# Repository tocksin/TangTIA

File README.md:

# TangTIA
Atari TIA monitor with Tang Nano for HDMI output

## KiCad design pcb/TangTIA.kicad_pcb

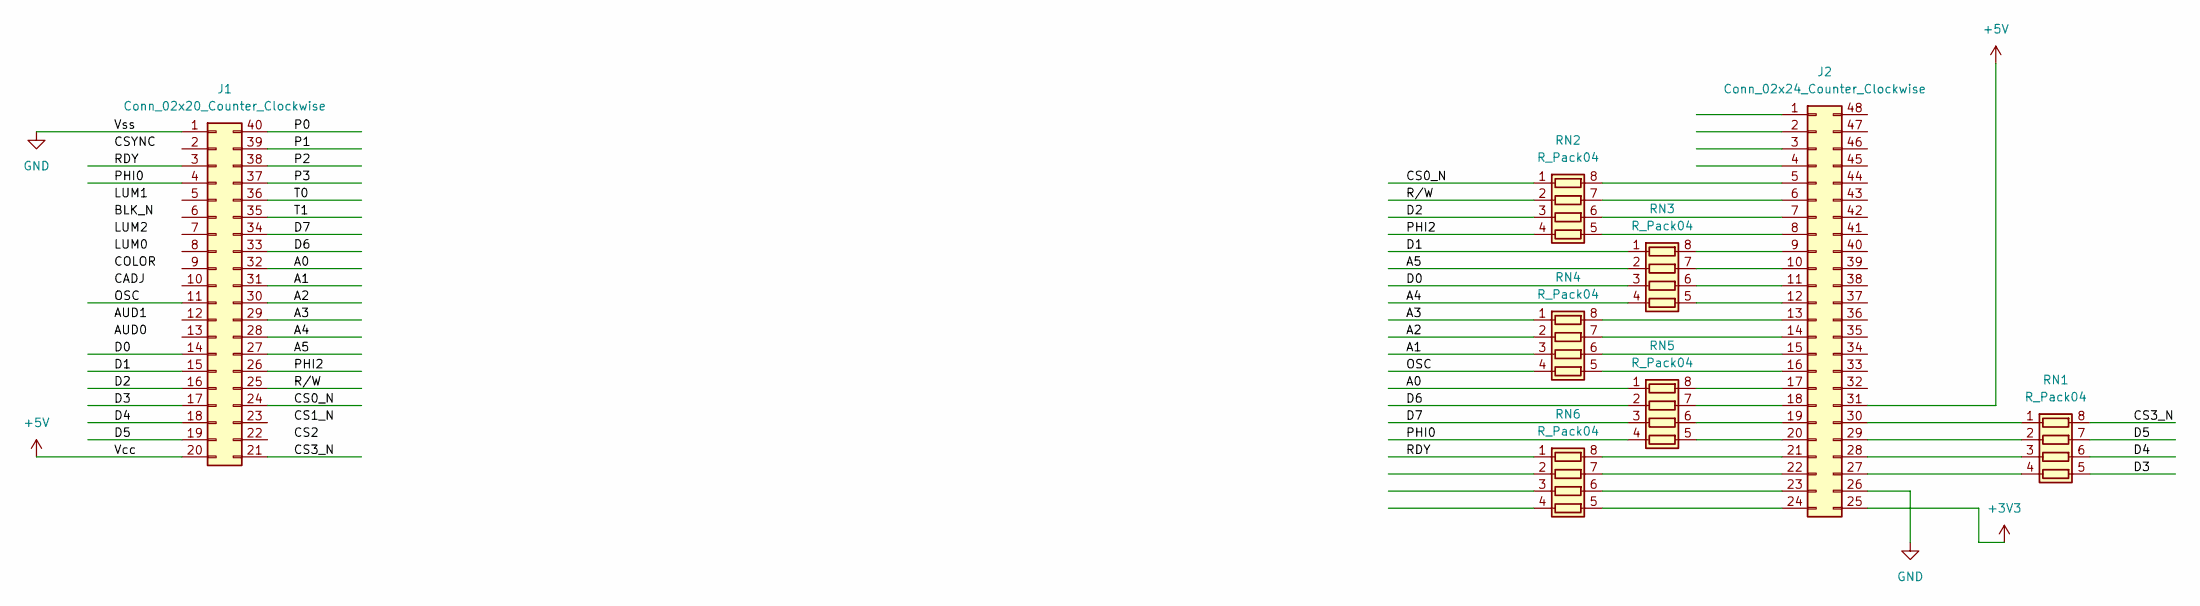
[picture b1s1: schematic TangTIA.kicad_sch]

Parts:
J1: Conn_02x20_Counter_Clockwise; DIP-40_W15.24mm_Socket_LongPads
J2: Conn_02x24_Counter_Clockwise; DIP-48_W15.24mm_Socket_LongPads
RN1, RN2, RN3, RN4, RN5, RN6: R_Pack04; RES_2012_S8V_5P08X2P2_PAN-M

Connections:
+3V3: J2.25
+5V: J1.20, J2.31
/A0: J1.32, RN5.1 (R1.1)
/A1: J1.31, RN4.3 (R3.1)
/A2: J1.30, RN4.2 (R2.1)
/A3: J1.29, RN4.1 (R1.1)
/A4: J1.28, RN3.4 (R4.1)
/A5: J1.27, RN3.2 (R2.1)
/CS0_N: J1.24, RN2.1 (R1.1)
/CS3_N: J1.21, RN1.8 (R1.2)
/D0: J1.14, RN3.3 (R3.1)
/D1: J1.15, RN3.1 (R1.1)
/D2: J1.16, RN2.3 (R3.1)
/D3: J1.17, RN1.5 (R4.2)
/D4: J1.18, RN1.6 (R3.2)
/D5: J1.19, RN1.7 (R2.2)
/D6: J1.33, RN5.2 (R2.1)
/D7: J1.34, RN5.3 (R3.1)
/OSC: J1.11, RN4.4 (R4.1)
/P0: J1.40
/P1: J1.39
/P2: J1.38
/P3: J1.37
/PHI0: J1.4, RN5.4 (R4.1)
/PHI2: J1.26, RN2.4 (R4.1)
/RDY: J1.3, RN6.1 (R1.1)
/R/W: J1.25, RN2.2 (R2.1)
/T0: J1.36
/T1: J1.35
GND: J1.1, J2.26
unnamed: J2.5, RN2.8 (R1.2)
unnamed: J2.6, RN2.7 (R2.2)
unnamed: J2.7, RN2.6 (R3.2)
unnamed: J2.8, RN2.5 (R4.2)
unnamed: J2.9, RN3.8 (R1.2)
unnamed: J2.10, RN3.7 (R2.2)
unnamed: J2.11, RN3.6 (R3.2)
unnamed: J2.12, RN3.5 (R4.2)
unnamed: J2.13, RN4.8 (R1.2)
unnamed: J2.14, RN4.7 (R2.2)
unnamed: J2.15, RN4.6 (R3.2)
unnamed: J2.16, RN4.5 (R4.2)
unnamed: J2.17, RN5.8 (R1.2)
unnamed: J2.18, RN5.7 (R2.2)
unnamed: J2.19, RN5.6 (R3.2)
unnamed: J2.20, RN5.5 (R4.2)
unnamed: J2.21, RN6.8 (R1.2)
unnamed: J2.22, RN6.7 (R2.2)
unnamed: J2.23, RN6.6 (R3.2)
unnamed: J2.24, RN6.5 (R4.2)
unnamed: J2.27, RN1.4 (R4.1)
unnamed: J2.28, RN1.3 (R3.1)
unnamed: J2.29, RN1.2 (R2.1)
unnamed: J2.30, RN1.1 (R1.1)

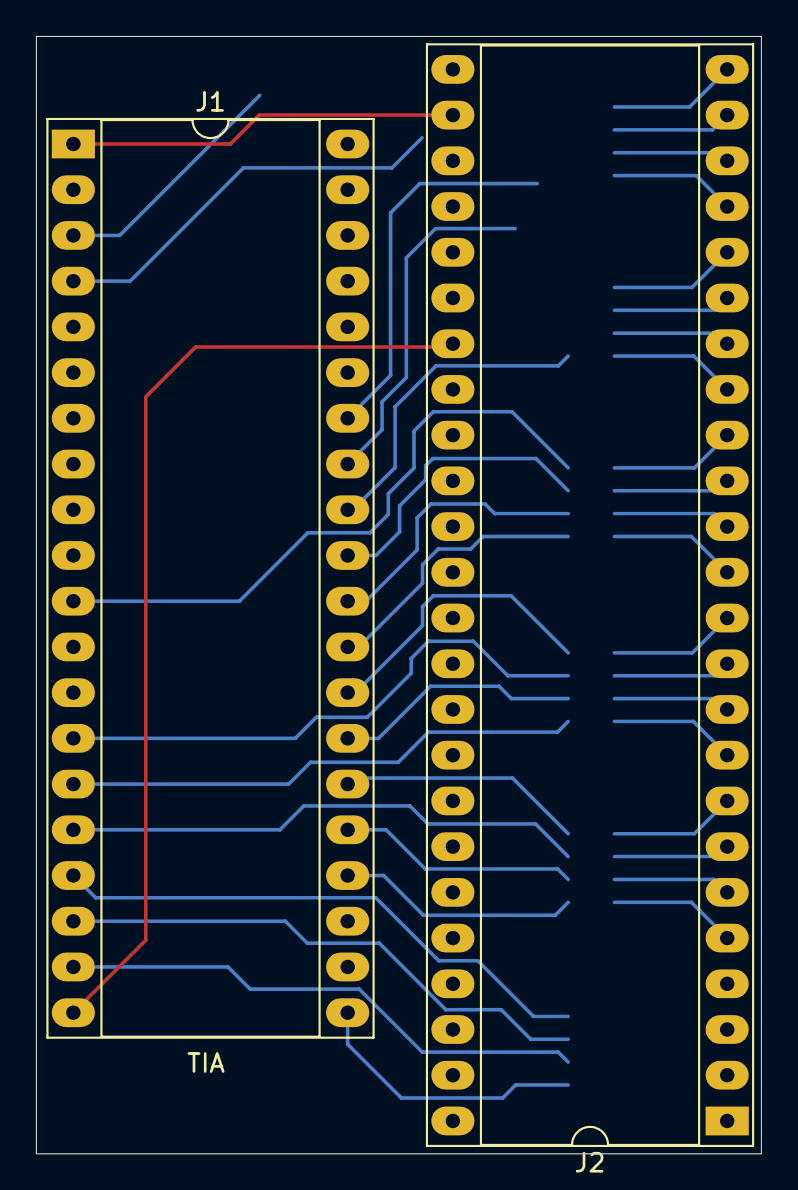
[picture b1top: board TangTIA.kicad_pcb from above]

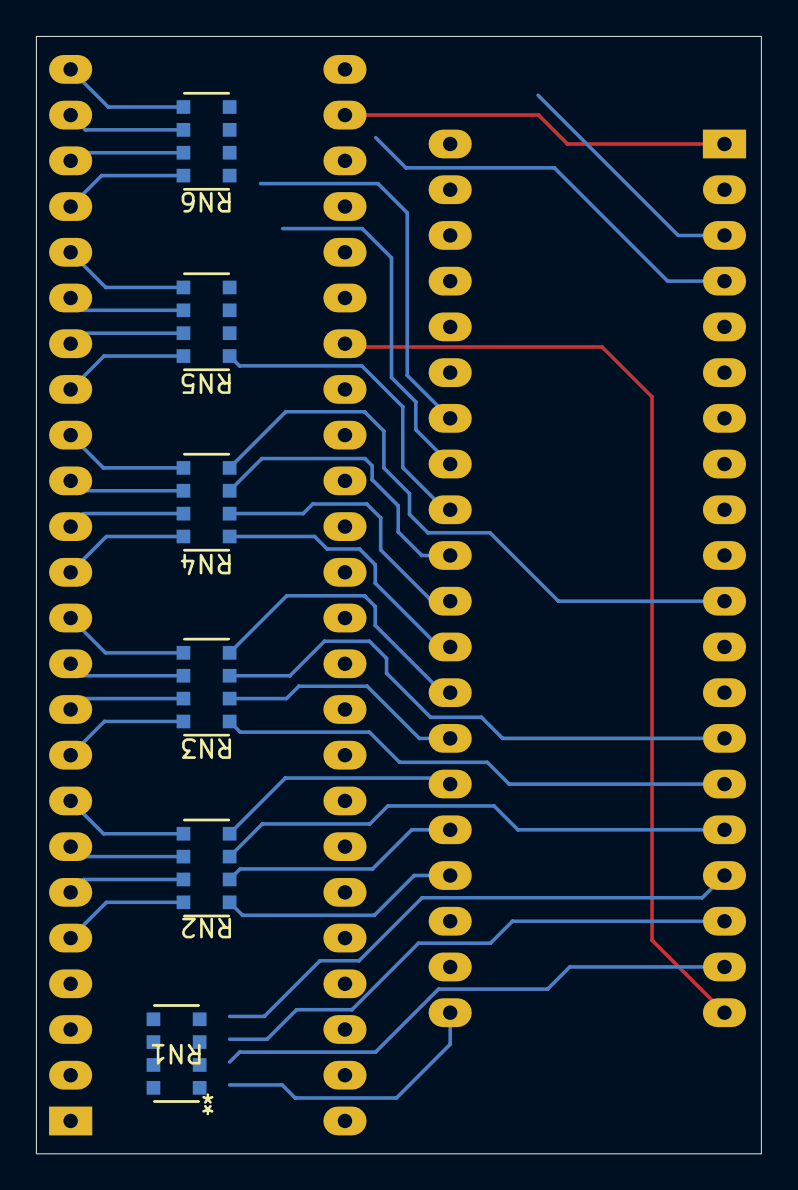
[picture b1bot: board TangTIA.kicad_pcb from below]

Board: 2 copper layers, 40.3 x 62.1 mm, 8 parts (6 on the bottom side), 47 nets.

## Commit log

2024-07-22 Add PCB files
2024-07-22 Add hdmi files and skeleton top
2024-07-23 Add test output for hdmi. Change pin names to meet code standard. Add lvds buffers.
2024-07-23 Remove reset pin assignment and replace with button only.
2024-07-24 Add pll ip module. add lvds buffers. add project files.
2024-07-25 Add missing GOWIN_UI define. Remove some pin constraints. Change MPSI pin modes.
2024-07-25 removed verilog files
2024-07-26 Add some references from other projects.
2024-07-26 Add register map for TIA. Tweak tools to allow for different address sizes.
2024-07-31 Add reference source files
2024-07-31 Copy settings from reference design into top
2024-07-31 Add notes on bus interface. tweak audio test.
2024-08-01 Add comments about ram interfacing
2024-08-01 Add comments/interface details to psram
2024-08-02 Generate new psram ip and place instance
2024-08-02 Add uarts for testing
2024-08-02 send test uart character
2024-08-02 Add uart receiver in echo mode
2024-08-02 Add UART interface to psram
2024-08-05 Add comments about clock design
2024-08-06 Change clock design to get both psram and hdmi working. add ip for plls and psram.
2024-08-06 remove incorrect comments
2024-08-06 Add comments about timing
2024-08-06 Add fifo/ram files
2024-08-06 Add uart_tx_fifo.vhd
2024-08-06 integrate uarts with psram
2024-08-06 add psram test to uart
2024-08-06 add skeleton code for TIA interface
2024-08-07 Add TIA information
2024-08-10 moving working reference files over to this project
2024-08-17 migrate working example psram code into project
2024-08-19 connect uart tx and rx to psram module. modify psram module to support one write, one read to support uart.
2024-08-19 Add comments about psram interface design
